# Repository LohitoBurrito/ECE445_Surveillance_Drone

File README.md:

## Abstract

The Early Response Drone aims to be a cost-effective drone system for early emergency reconnaissance. This drone, equipped with a camera and sensors, transmits real-time data such as video frames, altitude, and orientation to a user-friendly frontend interface via cellular connectivity. The system comprises four key components: a drone, backend, frontend, and cloud storage. Data captured by the drone is temporarily stored and processed for visual and analytical feedback. By integrating rapid deployment and reliable communication, the drone can assist in crime monitoring, fire hazard assessment, and medical triage, providing first responders with the critical information needed to make timely, informed decisions and improve overall emergency response outcomes. Although in-air trials were not performed to validate flight performance, the drone’s core software and electronics were thoroughly tested and demonstrated reliable functionality.

🚀 Check out our [Report](https://docs.google.com/document/d/1GGGv41obI-07fPF-_esPq27CqVMIz6DOAviRRR1eaIU/edit?tab=t.0) here

## Installation

### ① Initial Server Build

From your root directory of the project, run the following commands if you do not have the docker setup for our project.

```
 cd server
```

Create and run a docker container by building a docker image, create a docker network, and building a docker container. Make sure to replace {filepath} with the filepath to the project on your system. After running "docker run," a bash terminal corresponding to the docker container should open. 

```
 docker build -t drone_server_image .
```
```
 docker network create drone_network 
```
```
 docker run --name drone_server --network drone_network -p 5000:5000 -p 5001:5001 -v {filepath}\ECE445_SURVEILLANCE_DRONE:/workspace -it drone_server_image /bin/bash
```

Run the following commands to build the project.
```
 mkdir build
 cd build
```
```
 cmake ..
```
```
 make
```
```
 ./drone_server 0.0.0.0 5000 5001
```

### ② Future Server Build

Do not run if you completed the first step. Assuming that you already have the docker container, run the following commands from the root directory to re-run the server code. 
```
 cd server
```
```
 docker start -ai drone_server
```
```
 rm -rf build
 mkdir build
 cd build
```
```
 cmake ..
```
```
 make
```
```
 ./drone_server 0.0.0.0 5000 5001
```

### ③ Client Run

Ensure that you have installed nodeJS on your machine. On a seperate terminal from root directory of project, run the following commands to run the client application on your web browser.

```
 cd client
 npm install
 npm start
```

### ④ ESP Drone Run

Open the esp32_code folder in an arduino ide and flash an esp32 board with psram with the following code. We created our own esp32 flight controller, and all of the schematic and pcb files are within the kicad_files folder. The entire drone setup is described within the report link in the abstract of this readme and the independence c++ files.

## Some Test Videos:
📡 Watch our [Sensor Test](https://drive.google.com/file/d/1JHddWSbrLJgTwXRT1GT1PC6u4QnlyP4Z/view?usp=sharing) here

🤖 Watch our [Command Test](https://drive.google.com/file/d/1ZHc8pTtDRF40xnmZzDQPJSrRR4m5kNAQ/view?usp=sharing) here

Note: Yes, I know that the lin_accel has wrong units, and we updated the info. Also, we post-processed the lin_accel value wrong. The value must be divided by 2g to get the accurate acceleration value produced by the accelerometer inside the MPU6050 

Note: Also, the firebase database was taken down so the http urls do not work anymore

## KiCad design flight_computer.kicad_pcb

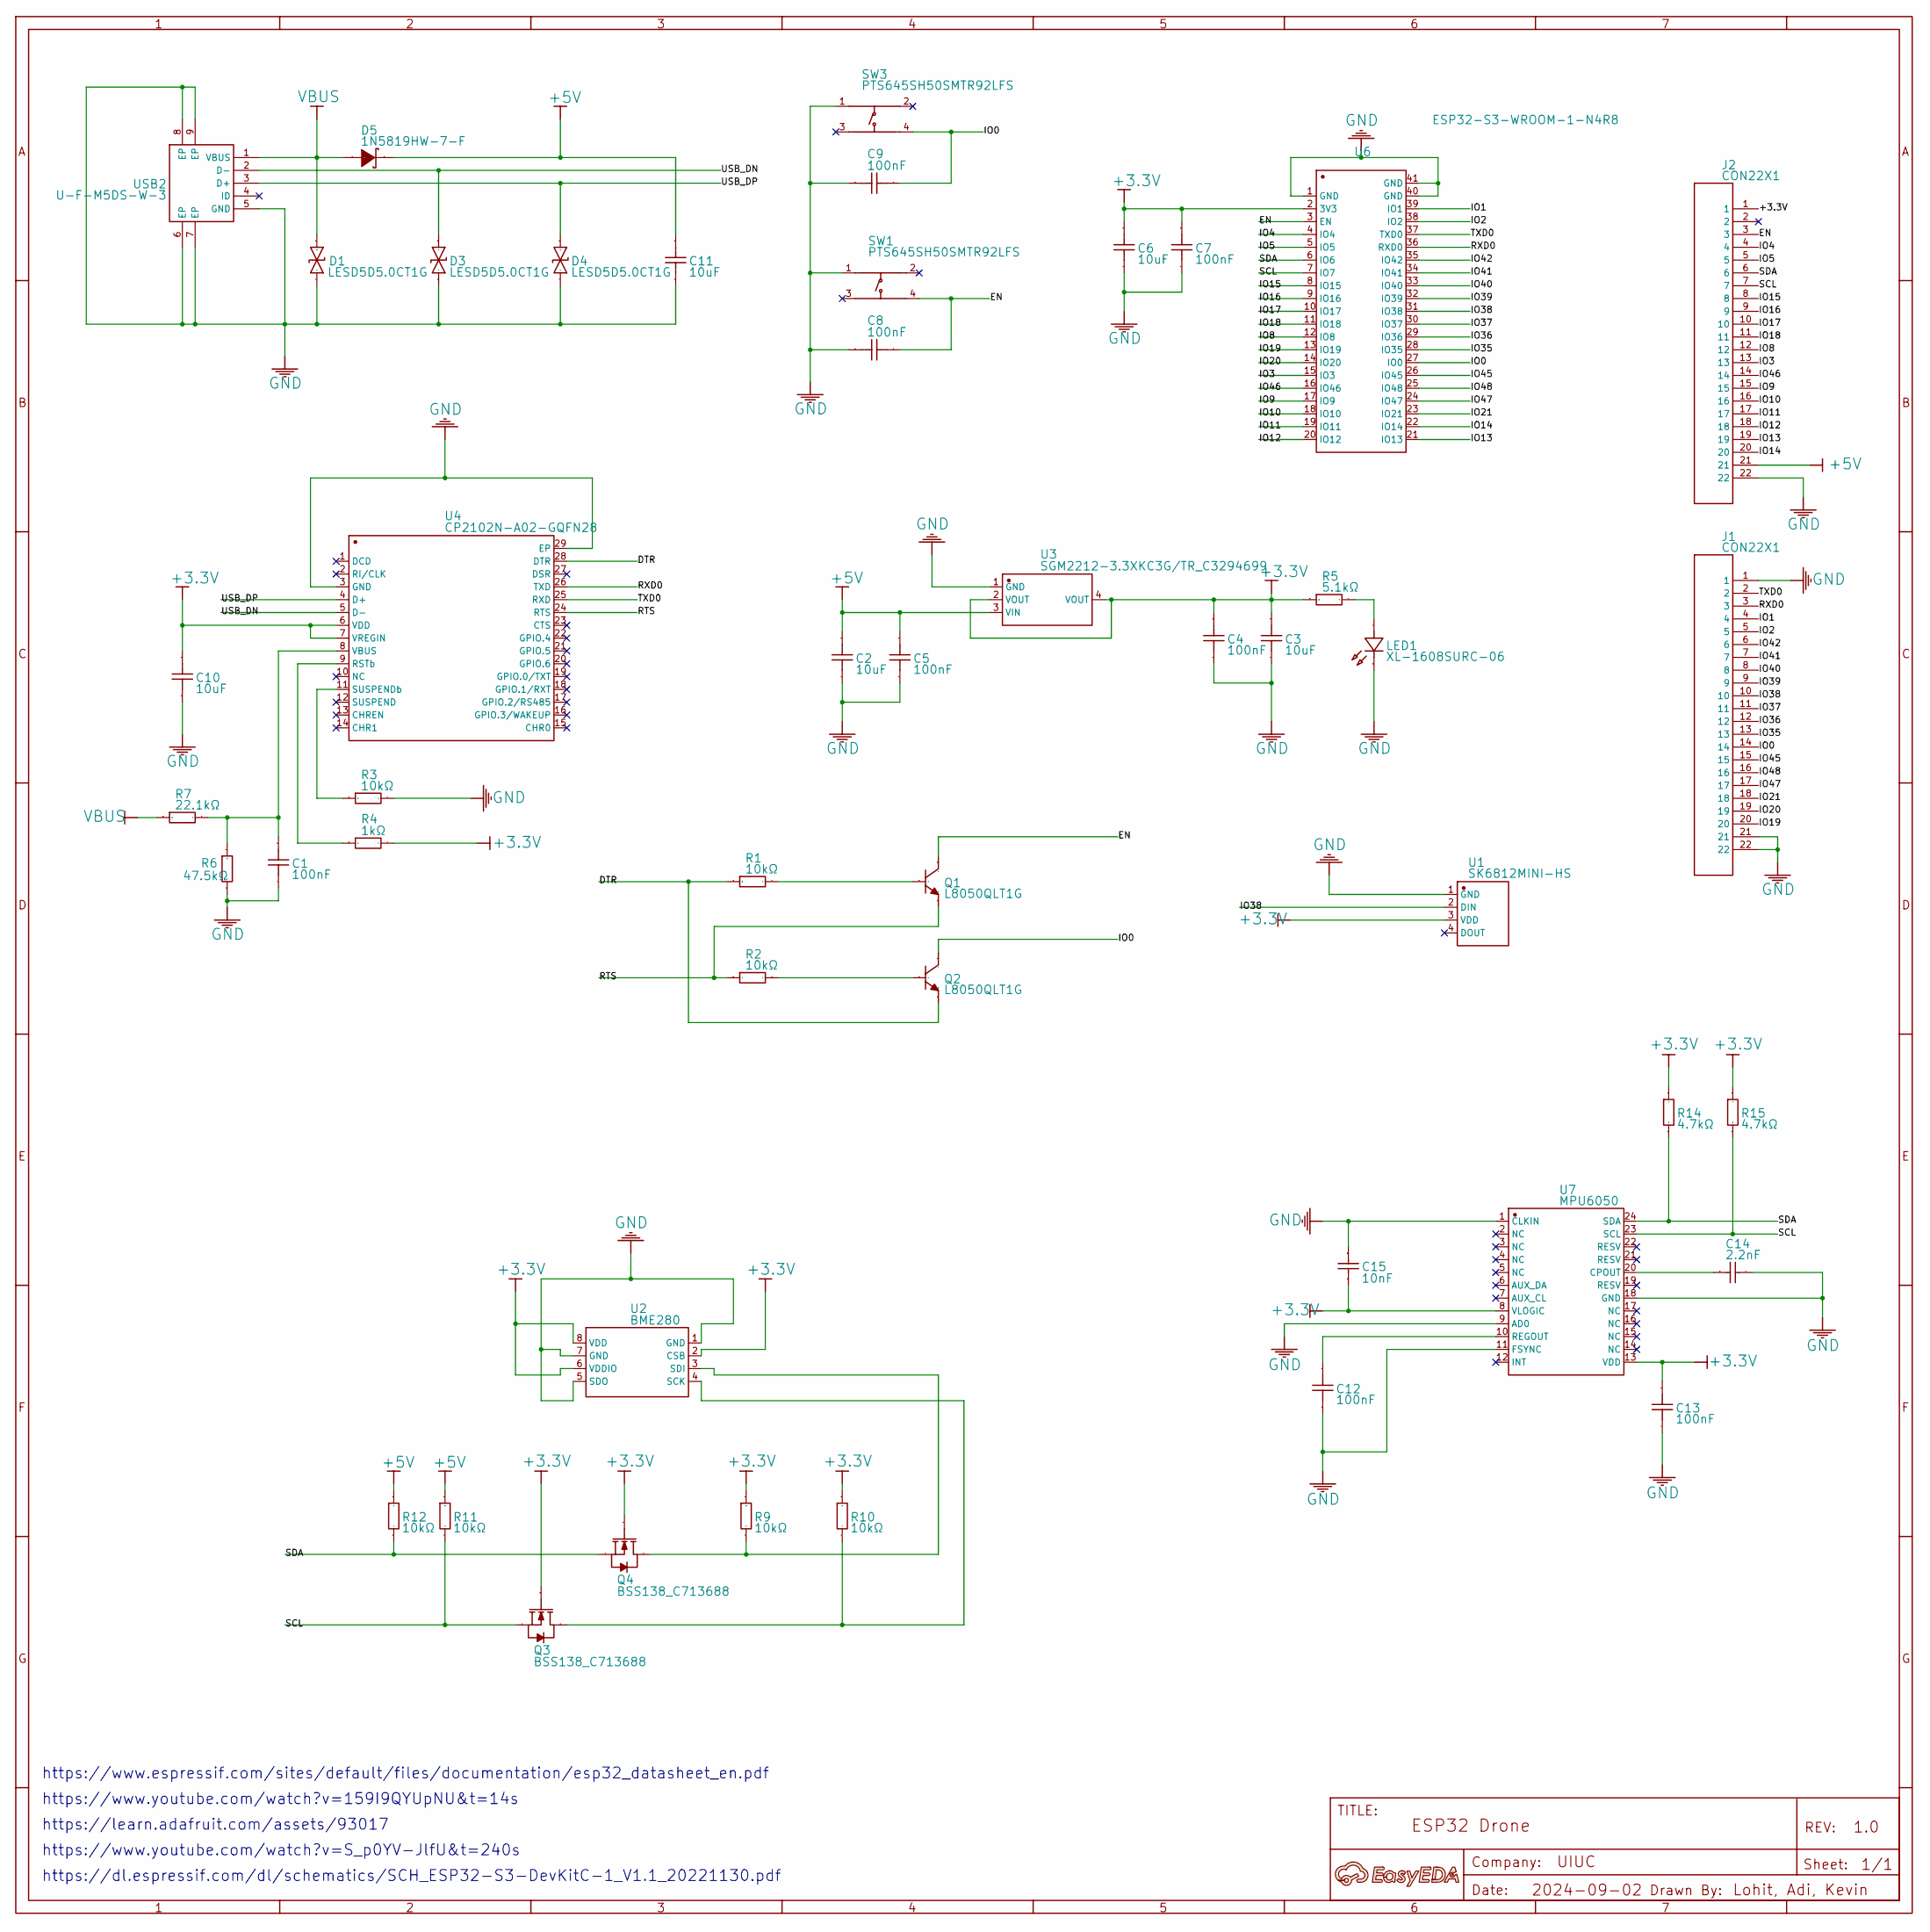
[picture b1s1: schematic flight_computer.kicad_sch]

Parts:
A1: A; Manufacturer Part ?
C1, C4, C5, C7, C8, C9, C12, C13: 100nF; Manufacturer Part CC0603KRX7R9BB104
C2, C3, C6, C10, C11: 10uF; Manufacturer Part CL10A106MA8NRNC
C14: 2.2nF; Manufacturer Part 0402B222K500NT
C15: 10nF; Manufacturer Part CC0603KRX7R9BB103
D1, D3, D4: LESD5D5.0CT1G; Manufacturer Part LESD5D5.0CT1G
D5: 1N5819HW-7-F; Manufacturer Part 1N5819HW-7-F
J1, J2: CON22X1
LED1: XL-1608SURC-06; Manufacturer Part XL-1608SURC-06
Q1, Q2: L8050QLT1G; Manufacturer Part L8050QLT1G
Q3, Q4: BSS138_C713688; Manufacturer Part BSS138
R1, R2, R3, R9, R10, R11, R12: 10kΩ; Manufacturer Part 0603WAF1002T5E
R4: 1kΩ; Manufacturer Part 0603WAF1001T5E
R5: 5.1kΩ; Manufacturer Part 0402WGF5101TCE
R6: 47.5kΩ; Manufacturer Part 0402WGF4752TCE
R7: 22.1kΩ; Manufacturer Part 0402WGF2212TCE
R14, R15: 4.7kΩ; Manufacturer Part RC0603FR-074K7L
SW1, SW3: PTS645SH50SMTR92LFS; Manufacturer Part PTS645SH50SMTR92LFS
U1: SK6812MINI-HS; Manufacturer Part SK6812MINI-HS
U2: BME280; Manufacturer Part BME280
U3: SGM2212-3.3XKC3G/TR_C3294699; Manufacturer Part SGM2212-3.3XKC3G/TR
U4: CP2102N-A02-GQFN28; Manufacturer Part CP2102N-A02-GQFN28
U6: ESP32-S3-WROOM-1-N4R8; Manufacturer Part ESP32-S3-WROOM-1-N4R8
U7: MPU6050; Manufacturer Part MPU6050_C9900042518
USB2: U-F-M5DS-W-3; Manufacturer Part U-F-M5DS-W-3

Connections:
+3.3V: C3.1, C4.1, C6.1, C7.1, C10.1, C13.1, C15.2, J2.1, Q3.1 (G), Q4.1 (G), R4.2, R5.1, R9.1, R10.1, R14.2, R15.2, U1.3 (VDD), U2.2 (CSB), U2.6 (VDDIO), U2.8 (VDD), U3.2 (VOUT), U3.4 (VOUT), U4.6 (VDD), U4.7 (VREGIN), U6.2 (3V3), U7.8 (VLOGIC), U7.13 (VDD)
+5V: C2.1, C5.1, C11.1, D5.1 (K), J2.21, R11.1, R12.1, U3.3 (VIN)
DTR: Q2.2 (E), R1.1, U4.28 (DTR)
EN: C8.2, J2.3, Q1.3 (C), SW1.4, U6.3 (EN)
GND: C1.2, C2.2, C3.2, C4.2, C5.2, C6.2, C7.2, C8.1, C9.1, C10.2, C11.2, C12.2, C13.2, C14.2, C15.1, D1.2, D3.2, D4.2, J1.1, J1.21, J1.22, J2.22, LED1.1 (K), R3.2, R6.2, SW1.1, SW3.1, U1.1 (GND), U2.1 (GND), U2.5 (SDO), U2.7 (GND), U3.1 (GND), U4.3 (GND), U4.29 (EP), U6.1 (GND), U6.40 (GND), U6.41 (GND), U7.1 (CLKIN), U7.9 (AD0), U7.11 (FSYNC), U7.18 (GND), USB2.5 (GND), USB2.6 (EP), USB2.7 (EP), USB2.8 (EP), USB2.9 (EP)
IO0: C9.2, J1.14, Q2.3 (C), SW3.4, U6.27 (IO0)
IO1: J1.4, U6.39 (IO1)
IO2: J1.5, U6.38 (IO2)
IO3: J2.13, U6.15 (IO3)
IO4: J2.4, U6.4 (IO4)
IO5: J2.5, U6.5 (IO5)
IO8: J2.12, U6.12 (IO8)
IO9: J2.15, U6.17 (IO9)
IO10: J2.16, U6.18 (IO10)
IO11: J2.17, U6.19 (IO11)
IO12: J2.18, U6.20 (IO12)
IO13: J2.19, U6.21 (IO13)
IO14: J2.20, U6.22 (IO14)
IO15: J2.8, U6.8 (IO15)
IO16: J2.9, U6.9 (IO16)
IO17: J2.10, U6.10 (IO17)
IO18: J2.11, U6.11 (IO18)
IO19: J1.20, U6.13 (IO19)
IO20: J1.19, U6.14 (IO20)
IO21: J1.18, U6.23 (IO21)
IO35: J1.13, U6.28 (IO35)
IO36: J1.12, U6.29 (IO36)
IO37: J1.11, U6.30 (IO37)
IO38: J1.10, U1.2 (DIN), U6.31 (IO38)
IO39: J1.9, U6.32 (IO39)
IO40: J1.8, U6.33 (IO40)
IO41: J1.7, U6.34 (IO41)
IO42: J1.6, U6.35 (IO42)
IO45: J1.15, U6.26 (IO45)
IO46: J2.14, U6.16 (IO46)
IO47: J1.17, U6.24 (IO47)
IO48: J1.16, U6.25 (IO48)
Q1_1: Q1.1 (B), R1.2
Q2_1: Q2.1 (B), R2.2
Q3_3: Q3.3 (D), R10.2, U2.4 (SCK)
Q4_3: Q4.3 (D), R9.2, U2.3 (SDI)
R3_1: R3.1, U4.11 (SUSPENDb)
R5_2: LED1.2 (A), R5.2
RTS: Q1.2 (E), R2.1, U4.24 (RTS)
RXD0: J1.3, U4.26 (TXD), U6.36 (RXD0)
SCL: J2.7, Q3.2 (S), R11.2, R15.1, U6.7 (IO7), U7.23 (SCL)
SDA: J2.6, Q4.2 (S), R12.2, R14.1, U6.6 (IO6), U7.24 (SDA)
TXD0: J1.2, U4.25 (RXD), U6.37 (TXD0)
U4_8: C1.1, R6.1, R7.2, U4.8 (VBUS)
U4_9: R4.1, U4.9 (RSTb)
U7_10: C12.1, U7.10 (REGOUT)
U7_20: C14.1, U7.20 (CPOUT)
USB_DN: D3.1, U4.5 (D-), USB2.2 (D-)
USB_DP: D4.1, U4.4 (D+), USB2.3 (D+)
VBUS: D1.1, D5.2 (A), R7.1, USB2.1 (VBUS)

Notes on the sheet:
https://www.youtube.com/watch?v=159I9QYUpNU&t=14s
https://dl.espressif.com/dl/schematics/SCH_ESP32-S3-DevKitC-1_V1.1_20221130.pdf
https://www.youtube.com/watch?v=S_p0YV-JlfU&t=240s
https://www.espressif.com/sites/default/files/documentation/esp32_datasheet_en.pdf
https://learn.adafruit.com/assets/93017

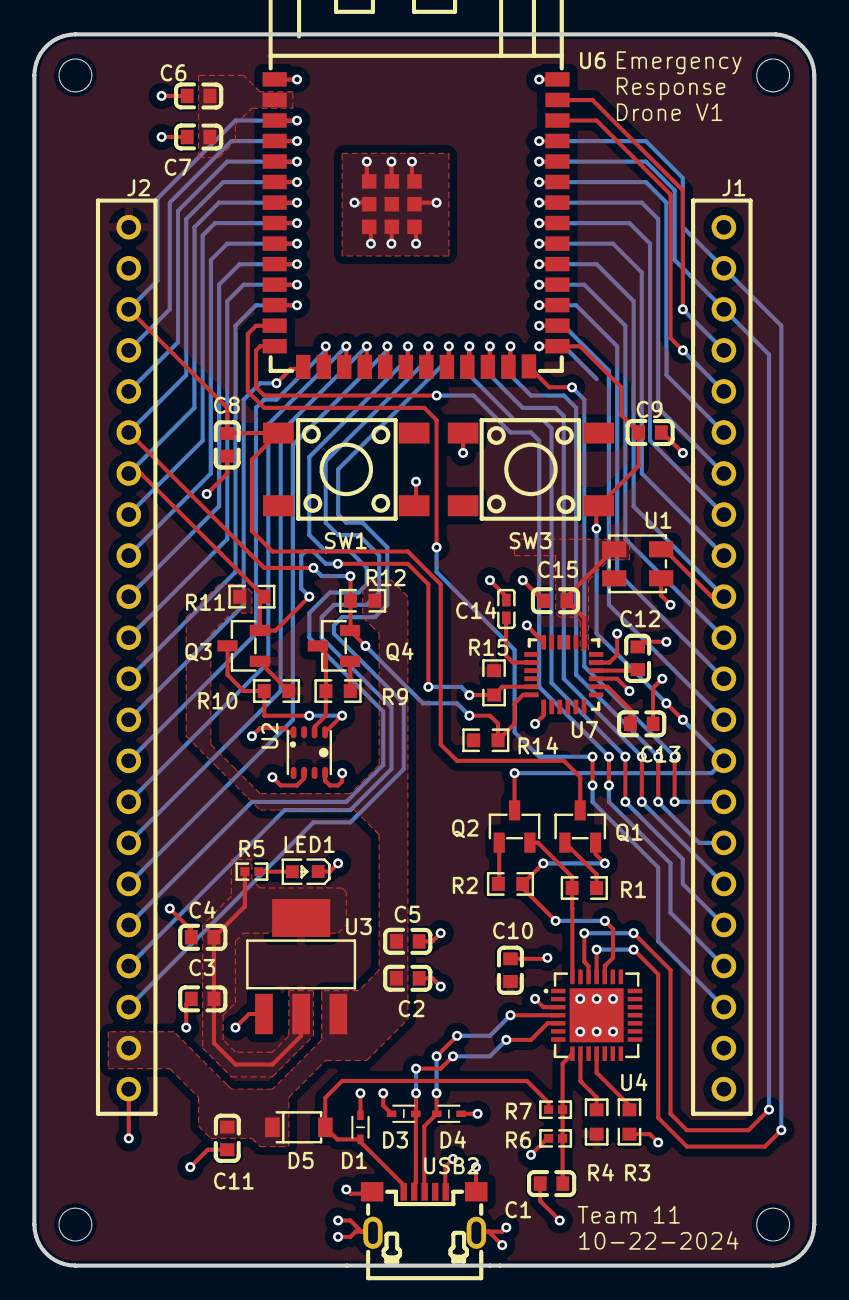
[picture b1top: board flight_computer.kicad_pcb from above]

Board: 2 copper layers, 48.3 x 76.2 mm, 52 parts (0 on the bottom side), 55 nets.

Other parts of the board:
Hole_gge7623: Hole_gge7623
Hole_gge7638: Hole_gge7638
Hole_gge7668: Hole_gge7668
Hole_gge7683: Hole_gge7683

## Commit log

2024-08-18 added initial client files
2024-08-19 client and server base setup
2024-08-19 added starter socket files w boost beast
2024-08-21 created command control untested
2024-08-24 working websockets
2024-08-24 enabled command queue to asynchronously recieve and send commands
2024-08-28 connected frontend with backend
2024-08-28 added ui update for keypress
2024-09-12 removed code
2024-09-12 removed .vscode
2024-12-25 Early Response Drone
2024-12-25 added schematic and pcb
2024-12-25 added videos
2024-12-25 videos
2024-12-25 added arduino files
2025-01-08 pushed files
2025-01-08 removed unnecessary files
2025-01-27 making first commits
2025-01-27 cleaning repository
2025-01-27 cmake build system
2025-03-08 Create LICENSE
